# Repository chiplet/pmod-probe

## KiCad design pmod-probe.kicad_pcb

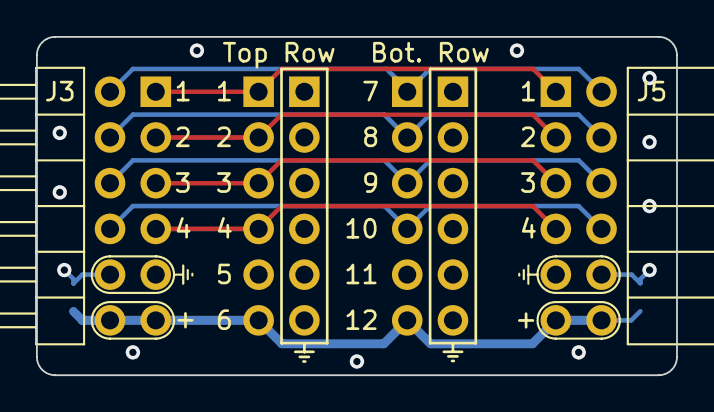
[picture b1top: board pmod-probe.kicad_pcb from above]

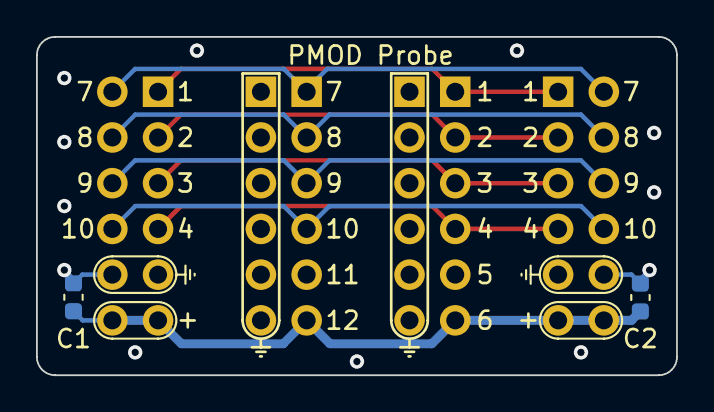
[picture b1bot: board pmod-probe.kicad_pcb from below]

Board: 4 copper layers, 35.6 x 18.8 mm, 8 parts (2 on the bottom side), 10 nets.

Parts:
C1, C2: 100n; C_0603_1608Metric
J1: Top; PinHeader_1x06_P2.54mm_Vertical
J2, J4: ProbeGrounds; PinHeader_1x06_P2.54mm_Vertical
J3: PMOD_Peripheral_Conn_02x06; PMOD_PinHeader_2x06_P2.54mm_Horizontal
J5: PMOD_Host_Conn_02x06; PMOD_PinSocket_2x06_P2.54mm_Horizontal
J6: Bottom; PinHeader_1x06_P2.54mm_Vertical

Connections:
GND: C1.2, C2.2, J1.5, J2.1, J2.2, J2.3, J2.4, J2.5, J2.6, J3.5 (GND), J3.11 (GND), J4.1, J4.2, J4.3, J4.4, J4.5, J4.6, J5.5 (GND), J5.11 (GND), J6.5
unnamed: J1.1, J3.1 (A0), J5.1 (A0)
unnamed: J1.2, J3.2 (A1), J5.2 (A1)
unnamed: J1.3, J3.3 (A2), J5.3 (A2)
unnamed: J1.4, J3.4 (A3), J5.4 (A3)
unnamed: J3.7 (B0), J5.7 (B0), J6.1
unnamed: J3.8 (B1), J5.8 (B1), J6.2
unnamed: J3.9 (B2), J5.9 (B2), J6.3
unnamed: J3.10 (B3), J5.10 (B3), J6.4
VCC: C1.1, C2.1, J1.6, J3.6 (VCC), J3.12 (VCC), J5.6 (VCC), J5.12 (VCC), J6.6

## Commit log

2022-05-18 Untrack backups
2022-05-18 Check in gerbers
2022-05-30 Create LICENSE
